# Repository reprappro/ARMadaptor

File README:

RepRapPro Ltd

Arduino DUE Sanguinololu Adaptor

Licence: GPL

Design: Adrian

Status: Pre-alpha - not yet made and tested.

Thanks to MAL's Adventures in Electronics Blog at 

http://circuitfun.wordpress.com/2012/01/02/arduino-mega-shield-template-in-eagle-improved/

for the Arduino sield blank design.

Simple PCBs to allow an Arduino DUE to be plugged into a Sanguinololu 
in place of its ATMEGA chip.  One is a shield for the Arduino that
has a pin header for a 20-way ribbon cable.  The other is a PCB that just
has a header for the other end of the ribbon connected to a set of pins that 
pretend to be the Sanguinololu's ATMEGA chip.  

The DUE pinouts are:

{X, Y, Z, [E]}
{Bed, Hot end}
-1 = not used

STEP_PINS {54, 60, 46, 26}
DIRECTION_PINS {55, 61, 48, 28}
ENABLE_PINS {38, -1, 62, -1}
STOP_PINS {3, 14, 17}
TEMP_SENSE_PINS {10, 9}  // Analogue pin numbers
HEAT_ON_PINS {8, 9}

Adrian
23 January 2013

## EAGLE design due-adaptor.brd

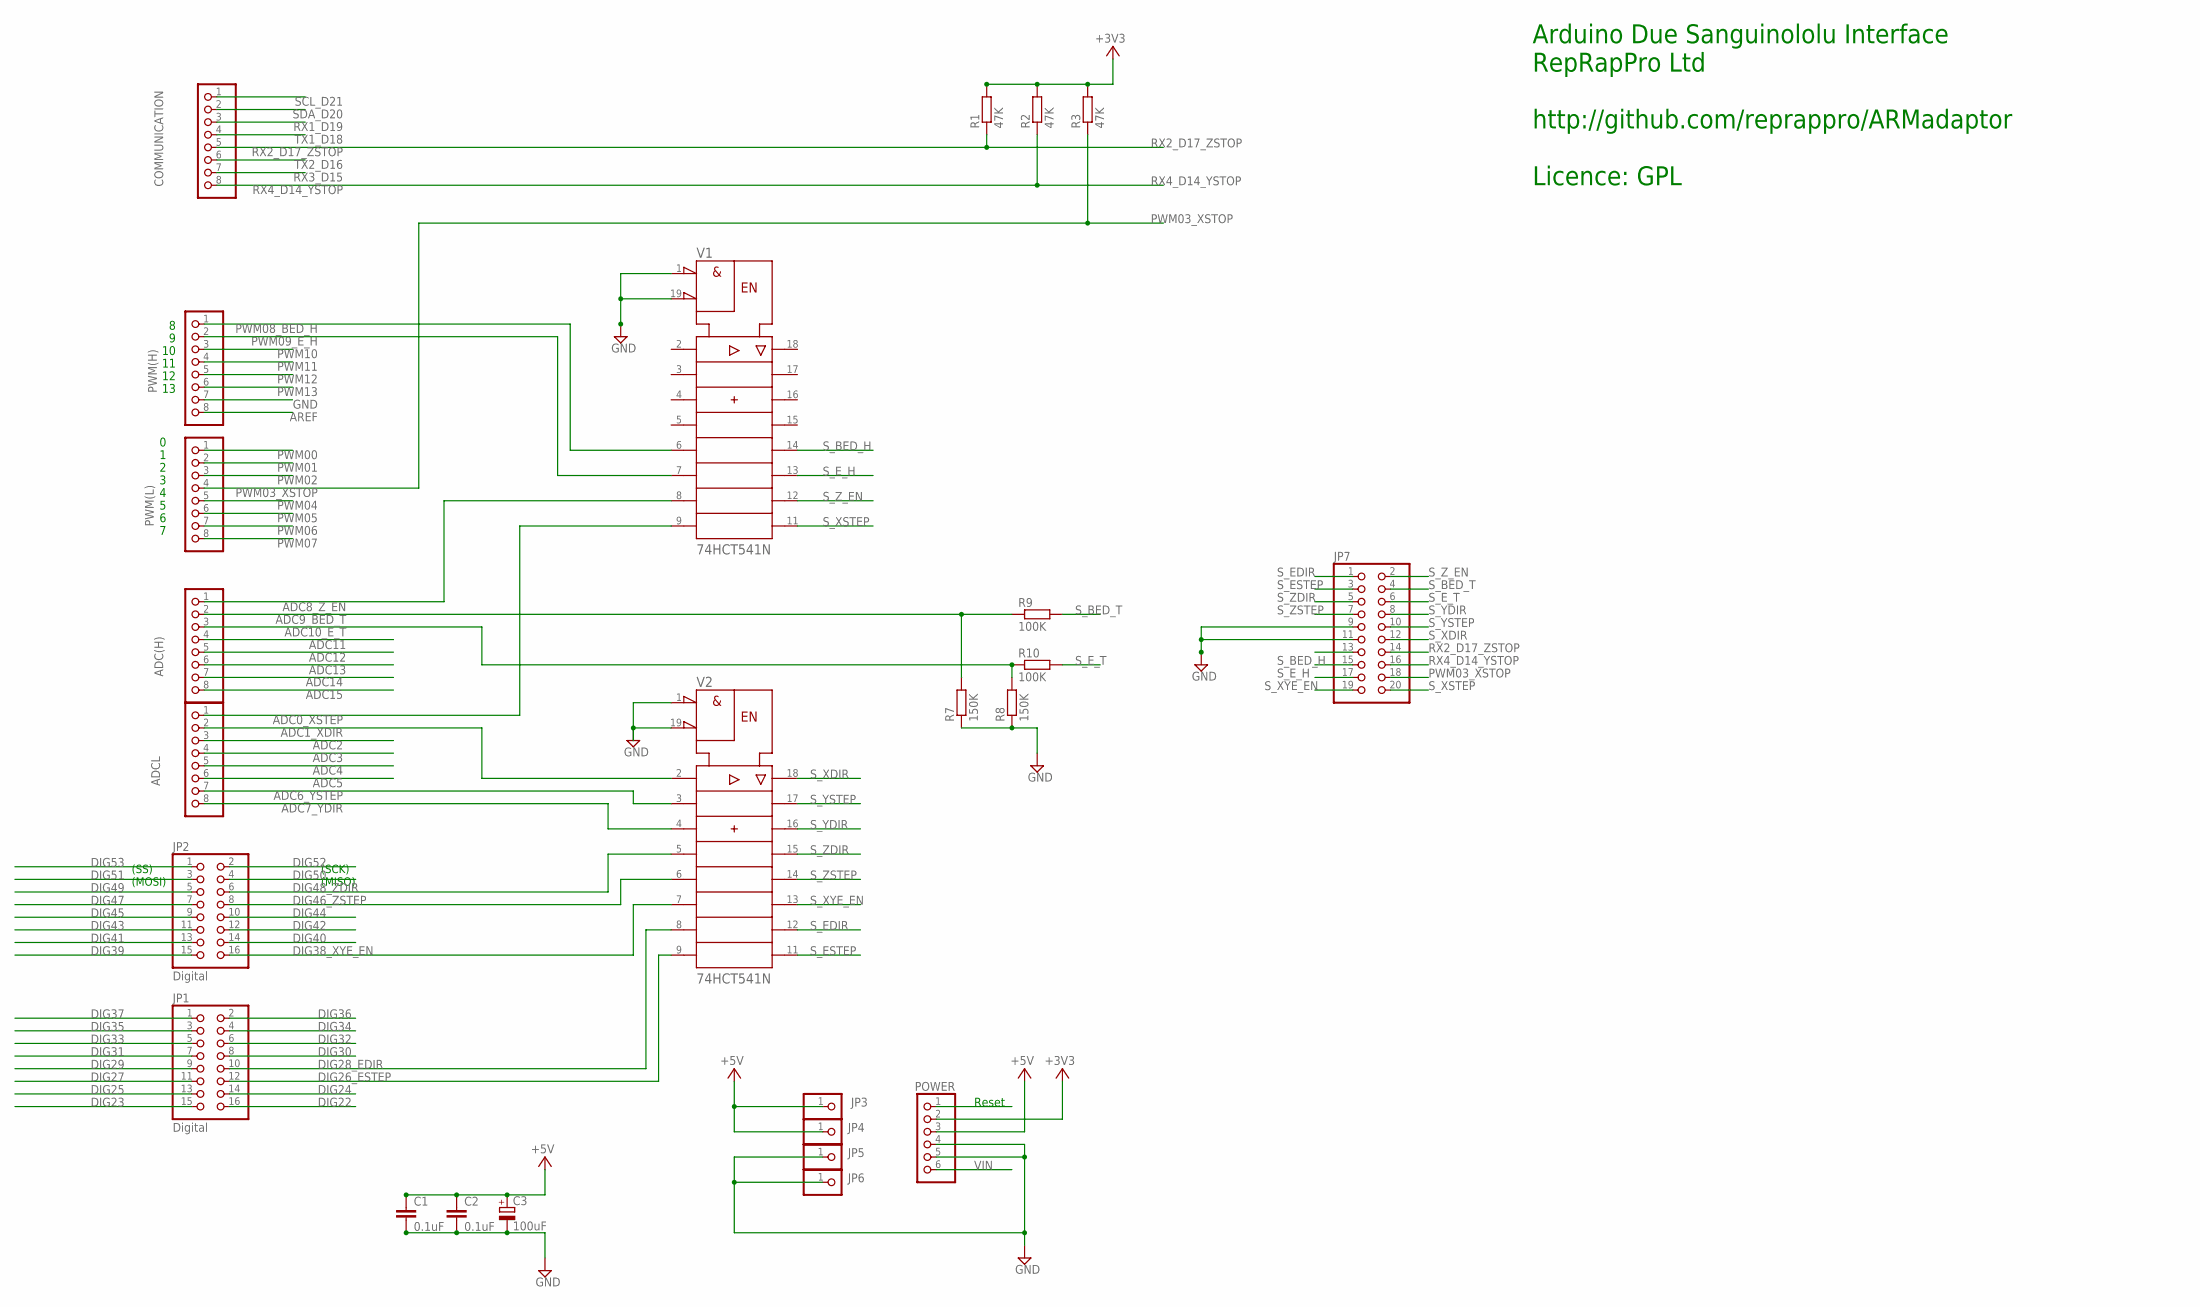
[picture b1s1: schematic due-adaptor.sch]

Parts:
ADC(H): PINHD-1X8; 1X08
ADCL: PINHD-1X8; 1X08
C1, C2: 0.1uF; C025-024X044
C3: 100uF; E5-4
COMMUNICATION: PINHD-1X8; 1X08
JP1, JP2: Digital; 2X08
JP3, JP4, JP5, JP6: PINHD-1X1; 1X01
JP7: PINHD-2X10; 2X10
POWER: PINHD-1X6; 1X06
PWM(H): PINHD-1X8; 1X08
PWM(L): PINHD-1X8; 1X08
R1, R2, R3: 47K; 0207/7
R7, R8: 150K; 0207/7
R9, R10: 100K; 0207/7
V1, V2: 74HCT541N; DIL20

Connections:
+3V3: POWER.2, R1.2, R2.2, R3.2
+5V: C1.1, C2.1, C3.+, JP3.1, JP4.1, POWER.3, V1.20 (+UB), V2.20 (+UB)
ADC0_XSTEP: ADCL.1, V1.9 (A8)
ADC1_XDIR: ADCL.2, V2.2 (A1)
ADC2: ADCL.3
ADC3: ADCL.4
ADC4: ADCL.5
ADC5: ADCL.6
ADC6_YSTEP: ADCL.7, V2.3 (A2)
ADC7_YDIR: ADCL.8, V2.4 (A3)
ADC8_Z_EN: ADC(H).1, V1.8 (A7)
ADC9_BED_T: ADC(H).2, R7.2, R9.1
ADC10_E_T: ADC(H).3, R8.2, R10.1
ADC11: ADC(H).4
ADC12: ADC(H).5
ADC13: ADC(H).6
ADC14: ADC(H).7
ADC15: ADC(H).8
AREF: PWM(H).8
DIG22: JP1.16
DIG23: JP1.15
DIG24: JP1.14
DIG25: JP1.13
DIG26_ESTEP: JP1.12, V2.9 (A8)
DIG27: JP1.11
DIG28_EDIR: JP1.10, V2.8 (A7)
DIG29: JP1.9
DIG30: JP1.8
DIG31: JP1.7
DIG32: JP1.6
DIG33: JP1.5
DIG34: JP1.4
DIG35: JP1.3
DIG36: JP1.2
DIG37: JP1.1
DIG38_XYE_EN: JP2.16, V2.7 (A6)
DIG39: JP2.15
DIG40: JP2.14
DIG41: JP2.13
DIG42: JP2.12
DIG43: JP2.11
DIG44: JP2.10
DIG45: JP2.9
DIG46_ZSTEP: JP2.8, V2.6 (A5)
DIG47: JP2.7
DIG48_ZDIR: JP2.6, V2.5 (A4)
DIG49: JP2.5
DIG50: JP2.4
DIG51: JP2.3
DIG52: JP2.2
DIG53: JP2.1
GND: C1.2, C2.2, C3.-, JP5.1, JP6.1, JP7.9, JP7.11, POWER.4, POWER.5, PWM(H).7, R7.1, R8.1, V1.1 (!G1), V1.10 (-UB), V1.19 (!G2), V2.1 (!G1), V2.10 (-UB), V2.19 (!G2)
PWM00: PWM(L).1
PWM01: PWM(L).2
PWM02: PWM(L).3
PWM03_XSTOP: JP7.18, PWM(L).4, R3.1
PWM04: PWM(L).5
PWM05: PWM(L).6
PWM06: PWM(L).7
PWM07: PWM(L).8
PWM08_BED_H: PWM(H).1, V1.6 (A5)
PWM09_E_H: PWM(H).2, V1.7 (A6)
PWM10: PWM(H).3
PWM11: PWM(H).4
PWM12: PWM(H).5
PWM13: PWM(H).6
RESET: POWER.1
RX1_D19: COMMUNICATION.3
RX2_D17_ZSTOP: COMMUNICATION.5, JP7.14, R1.1
RX3_D15: COMMUNICATION.7
RX4_D14_YSTOP: COMMUNICATION.8, JP7.16, R2.1
SCL_D21: COMMUNICATION.1
SDA_D20: COMMUNICATION.2
S_BED_H: JP7.15, V1.14 (Y5)
S_BED_T: JP7.4, R9.2
S_EDIR: JP7.1, V2.12 (Y7)
S_ESTEP: JP7.3, V2.11 (Y8)
S_E_H: JP7.17, V1.13 (Y6)
S_E_T: JP7.6, R10.2
S_XDIR: JP7.12, V2.18 (Y1)
S_XSTEP: JP7.20, V1.11 (Y8)
S_XYE_EN: JP7.19, V2.13 (Y6)
S_YDIR: JP7.8, V2.16 (Y3)
S_YSTEP: JP7.10, V2.17 (Y2)
S_ZDIR: JP7.5, V2.15 (Y4)
S_ZSTEP: JP7.7, V2.14 (Y5)
S_Z_EN: JP7.2, V1.12 (Y7)
TX1_D18: COMMUNICATION.4
TX2_D16: COMMUNICATION.6
VIN: POWER.6

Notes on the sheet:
Arduino Due Sanguinololu Interface RepRapPro Ltd http://github.com/reprappro/ARMadaptor Licence: GPL
(SS)
(MOSI)
(SCK)
(MISO)
Reset

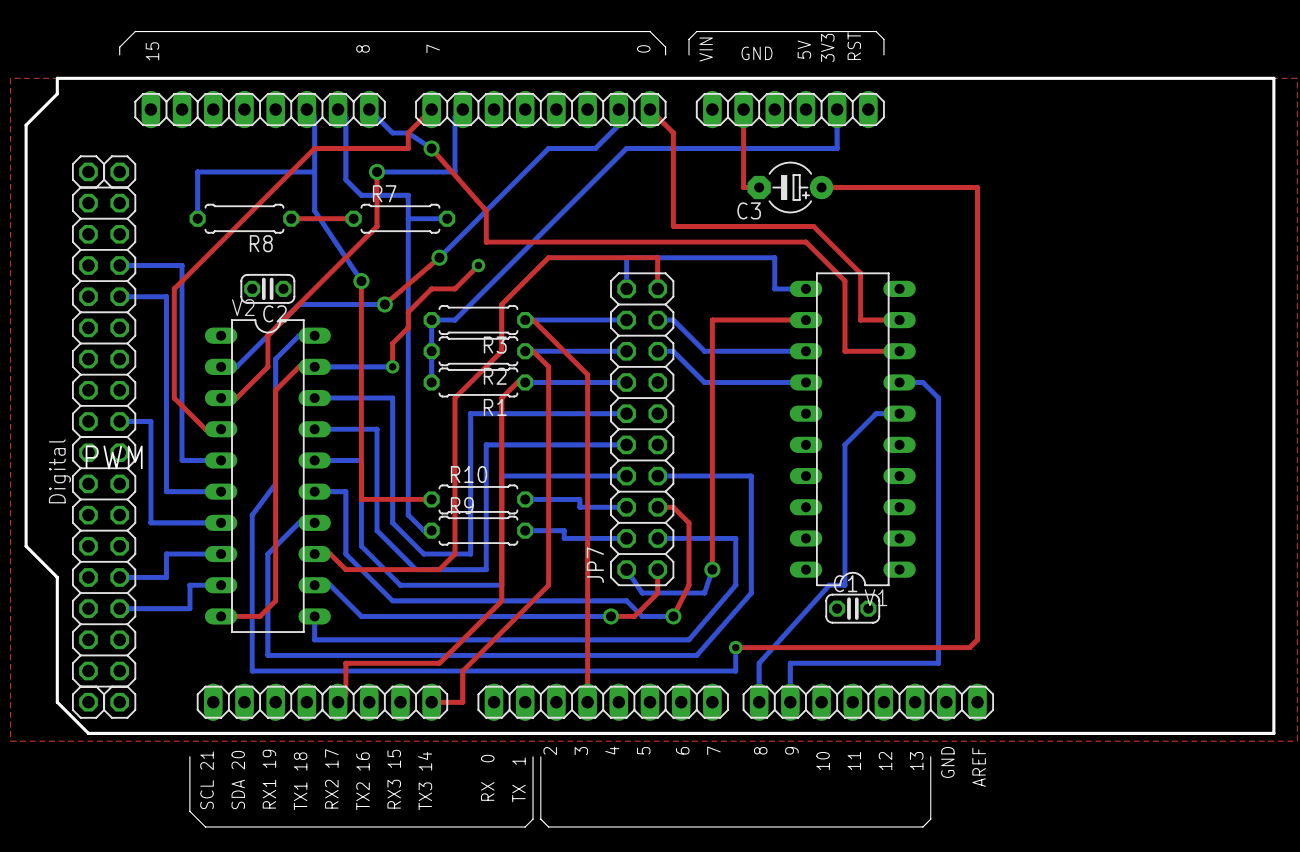
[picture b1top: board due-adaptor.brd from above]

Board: 2 copper layers, 101.6 x 65.1 mm, 25 parts (0 on the bottom side), 34 nets.

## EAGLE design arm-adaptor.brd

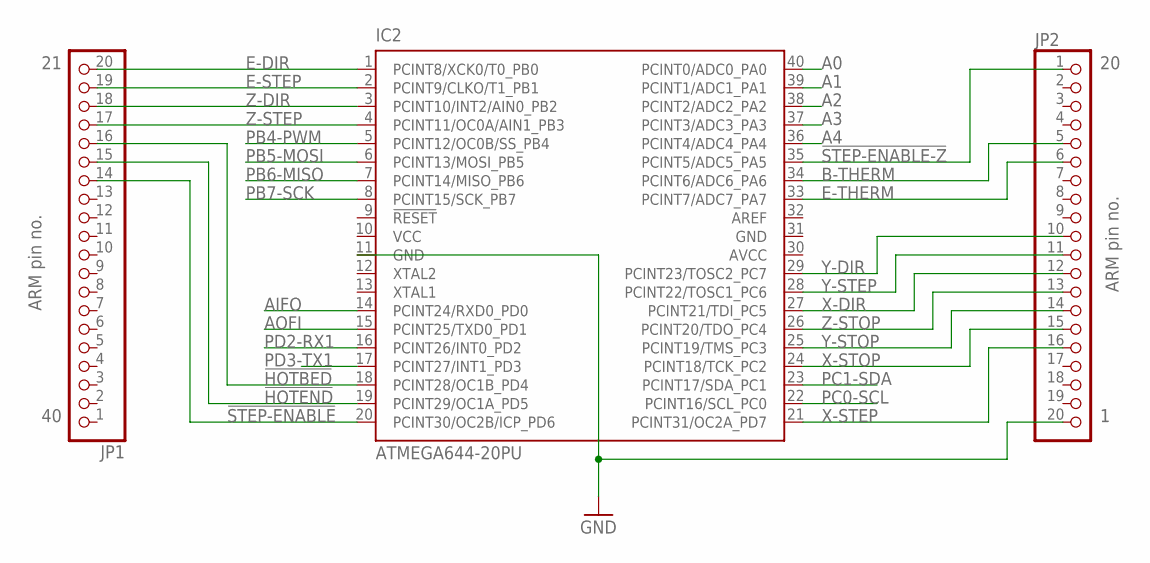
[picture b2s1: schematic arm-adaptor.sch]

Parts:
IC2: ATMEGA644-20PU; DIL40
JP1, JP2: PINHD-1X20; 1X20

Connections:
!HOTBED: IC2.18 (PCINT28/OC1B_PD4), JP1.16
!HOTEND: IC2.19 (PCINT29/OC1A_PD5), JP1.15
!STEP-ENABLE: IC2.20 (PCINT30/OC2B/ICP_PD6), JP1.14
!STEP-ENABLE-Z: IC2.35 (PCINT5/ADC5_PA5), JP2.1
A0: IC2.40 (PCINT0/ADC0_PA0)
A1: IC2.39 (PCINT1/ADC1_PA1)
A2: IC2.38 (PCINT2/ADC2_PA2)
A3: IC2.37 (PCINT3/ADC3_PA3)
A4: IC2.36 (PCINT4/ADC4_PA4)
AIFO: IC2.14 (PCINT24/RXD0_PD0)
AOFI: IC2.15 (PCINT25/TXD0_PD1)
AVCC: IC2.30 (AVCC)
B-THERM: IC2.34 (PCINT6/ADC6_PA6), JP2.5
E-DIR: IC2.1 (PCINT8/XCK0/T0_PB0), JP1.20
E-STEP: IC2.2 (PCINT9/CLKO/T1_PB1), JP1.19
E-THERM: IC2.33 (PCINT7/ADC7_PA7), JP2.6
GND: IC2.11 (GND), IC2.31 (GND), JP2.20
PB4-PWM: IC2.5 (PCINT12/OC0B/SS_PB4)
PB5-MOSI: IC2.6 (PCINT13/MOSI_PB5)
PB6-MISO: IC2.7 (PCINT14/MISO_PB6)
PB7-SCK: IC2.8 (PCINT15/SCK_PB7)
PC0-SCL: IC2.22 (PCINT16/SCL_PC0)
PC1-SDA: IC2.23 (PCINT17/SDA_PC1)
PD2-RX1: IC2.16 (PCINT26/INT0_PD2)
PD3-TX1: IC2.17 (PCINT27/INT1_PD3)
VCC: IC2.10 (VCC)
X-DIR: IC2.27 (PCINT21/TDI_PC5), JP2.12
X-STEP: IC2.21 (PCINT31/OC2A_PD7), JP2.16
X-STOP: IC2.24 (PCINT18/TCK_PC2), JP2.15
Y-DIR: IC2.29 (PCINT23/TOSC2_PC7), JP2.10
Y-STEP: IC2.28 (PCINT22/TOSC1_PC6), JP2.11
Y-STOP: IC2.25 (PCINT19/TMS_PC3), JP2.14
Z-DIR: IC2.3 (PCINT10/INT2/AIN0_PB2), JP1.18
Z-STEP: IC2.4 (PCINT11/OC0A/AIN1_PB3), JP1.17
Z-STOP: IC2.26 (PCINT20/TDO_PC4), JP2.13

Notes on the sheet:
ARM pin no.

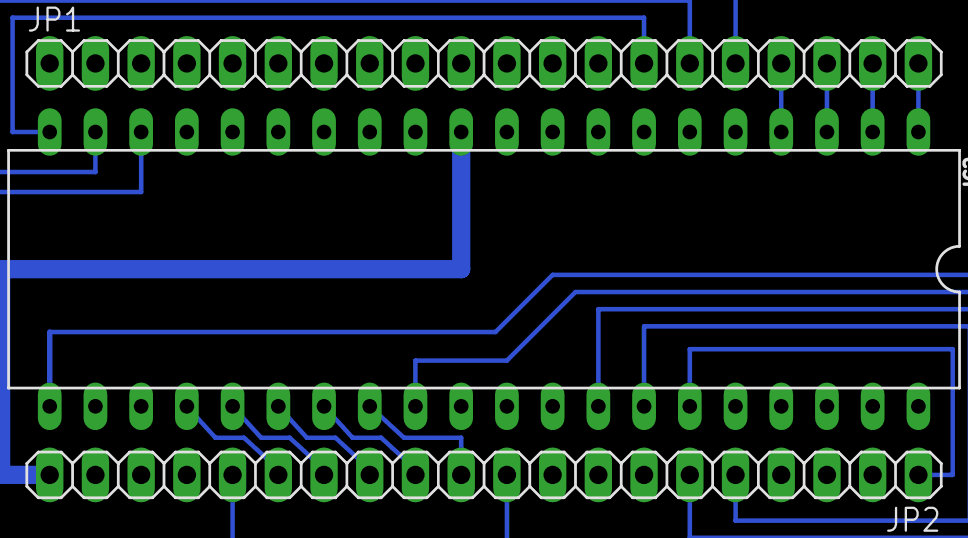
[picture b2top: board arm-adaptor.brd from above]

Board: 2 copper layers, 3 parts (0 on the bottom side), 18 nets.

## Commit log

2012-09-15 ARM adaptor - first hack.
2012-09-17 Added SD card and potential dividers on analogue inputs.
2012-10-09 Minor mods to rotate SD holder to make it easier to insert the card.
2012-10-09 Removing temp files.
2012-10-09 README updated.
2012-10-09 README further updated.
2013-01-23 Design for Arduino DUE shield -> Sanguinololu.
2013-01-24 Updated README.
2013-06-08 0.1u caps added on endstop switches.
2013-06-08 Cleanup.
